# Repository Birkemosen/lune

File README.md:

# Lune V6

Local 6-zone hydronic manifold controller (ESP32-S3 / ESPHome). Safe without a
coordinator: motors, endstops, temperature freshness, and command clamps run on
the device.

**Documentation:** [docs/README.md](docs/README.md) — index of all V6 documentation, with links to Lune Touch and the design system.

> **Status (October 2026): pre-release, in field validation.**
>
> | Area | State |
> |---|---|
> | Firmware | `v1.0.0` development builds; no public release yet |
> | Hardware | Rev 3.3 is the only supported board |
> | Valve control | Endstop detection, working-range learning and motor fault handling in place |
> | Web UI | Local web UI (EN/DA): Home, a sheet per zone and the manifold, and System (connections, firmware, backup, service, Motor Lab) |
> | Integration | `/api/v1` with Touch authority lease, Asgard heat-pump coordination and external room temperatures |
> | Implementation plan | Phases 0–8 complete; phase 9 (staged field rollout and outcome measurement) in progress |
>
> Expect breaking changes to the API and persisted settings until `v1.0.0` is tagged.

## Layout

```text
lune-v6/                 Firmware, local dashboard, hardware, tests
  configurations/        Device YAML entrypoints
  packages/              Board / hardware / network / zones
  components/            Custom C++ (lv6_*)
  web/                   Design System 2 UI (see below)
  docs/                  Manual, API, architecture
shared/contracts/        Cross-product contracts (e.g. room physics)
docs/                    Cross-device notes
```

Related repositories:

- [`Birkemosen/lune-coordinator`](https://github.com/Birkemosen/lune-coordinator) —
  Lune Touch / Mini, the whole-house coordinator.
- [`Birkemosen/lune-design-system`](https://github.com/Birkemosen/lune-design-system) —
  shared UI tokens and CSS. The web UI build expects it as a sibling checkout at
  `../lune-design-system`.

## Web UI (Lune Design System)

Home / sheets / System on the Lune design system: static HTML/CSS with radio navigation;
a thin binder paints live `/api/v1` data.
No ESPHome entity REST from the UI.

```text
lune-v6/web/
  build_ui.py       i18n shell → ui/{en,da}/
  i18n/             en / da catalogues
  binder-src/       esbuild → ui/binder.js (+ dashboard.js alias)
  ui/               Built CSS, HTML, binder (embedded in firmware)
  preview.html      Local mock preview
```

```bash
make design-tokens     # → lune-v6/web/ui/lune-ui.css
make dashboard-build   # HTML + binder + preview.html
```

Preview without a device:

```bash
python3 -m http.server 8765 -d lune-v6/web
# → http://127.0.0.1:8765/preview.html
```

Installer help: [`lune-v6/docs/Manual.md`](lune-v6/docs/Manual.md) (linked from in-UI `?`).

## Hardware (rev 3.3)

Current board package: `lune-v6/packages/board/lune-v6-rev33.yaml` (`rev33_gpio`).
Two-layer USB-C ESP32-S3-WROOM-1-N8R8 controller, six 3.3 V valve channels
(3× DRV8411 + hardware one-hot decoder), shared high-side sense for ADC /
ripple / overcurrent. Hostname: `lune-v6-<mac>` (revision is not part of the
name).

See [`lune-v6/README.md`](lune-v6/README.md) and
[`lune-v6/hardware/lune-v6-rev3.3/`](lune-v6/hardware/lune-v6-rev3.3/) for the
revision table, ECO level, and firmware integration. The firmware is for Rev 3.3
only and refuses to drive motors on an older board — pin maps collide.

Validate the schematic:

```bash
python3 lune-v6/hardware/lune-v6-rev3.3/check_design.py
```

## Setup and commands

```bash
python3.13 -m venv .venv313
./.venv313/bin/python -m pip install -r requirements.txt
```

From the repository root (defaults to Lune V6):

```bash
make config
make dashboard-build
make build
make test
make deploy HOST=192.168.x.x
```

Device-local:

```bash
make -C lune-v6 help
make -C lune-v6 test
```

Release firmware (no WiFi secrets) → gitignored `lune-v6/dist/`:

```bash
make release-firmware VERSION=v1.0.0
```

`secrets.yaml` stays at the repo root and is gitignored.

## Boundaries

- V6 validates and clamps every command locally.
- Touch sends setpoints / weather preload — not zone choice for room temperatures.
- External hubs POST `/api/v1/room-temperatures` with `sensor_id`; V6 maps to zones.
- Shared physics contract: [`shared/contracts/lune_room_physics_contract_v1.md`](shared/contracts/lune_room_physics_contract_v1.md).

## License

| Part | License |
|---|---|
| Firmware, web UI, scripts and documentation — everything not listed below | [GPL-3.0-or-later](LICENSE) |
| Hardware design in [`lune-v6/hardware/`](lune-v6/hardware/) — EasyEDA project, schematics, design contract, layout and review documents | [CC BY-NC-SA 4.0](lune-v6/hardware/LICENSE) |

Third-party files keep their own licenses — notably the ESPHome agent skill in
[`.agents/skills/esphome/`](.agents/skills/esphome/) (MIT).

You may build, modify and share the firmware under the GPL; derived firmware must stay
open under the same terms. The firmware is built on ESPHome, whose runtime is GPLv3.

The hardware design is **non-commercial**. As the licensor I read that as follows:

- **Allowed:** private individuals may have boards made — by a PCB fab or assembly
  service ordering on their behalf — and use them in their own home. Fabs sell in
  minimum batches, so passing surplus boards from your own order to other private
  individuals is fine **at cost or for free**, as long as nobody makes money on it.
- **Not allowed without a commercial license:** selling boards, kits or installed systems
  for profit, offering them as part of a paid service or installation, or any other use
  aimed at earning money from the design.

Modified designs must be shared under the same license. If you want to use the design
commercially, ask through [GitHub](https://github.com/Birkemosen).

## Name

"Lune" and "Lune V6" identify this project. Forks are welcome under the licenses above,
but please give them a different name and do not present them, or products built on
them, as Lune or as endorsed by this project.

## Support the project

Lune is developed in spare time and paid for out of pocket. If it heats your floors and
you want to give something back, you can sponsor it through
[GitHub Sponsors](https://github.com/sponsors/Birkemosen).

If you build a Lune V6, a small one-time thank-you is welcome but never expected.
Sponsoring comes with no rewards or promises: Lune is built at its own pace.

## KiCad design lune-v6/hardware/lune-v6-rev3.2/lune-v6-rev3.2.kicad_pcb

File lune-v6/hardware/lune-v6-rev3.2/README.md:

# Lune V6 Rev 3.2

Status: ECO level **rev3.2-H**; PCB placed and routed; DRC, fabrication export
and physical qualification pending.

**Source of truth: `EasyEdaPro/lune-v6-rev3.2.eprj`, PCB document `pcb1_1`.**
Rev 3.2 was authored in KiCad through ECO rev3.2-B and every ECO from rev3.2-C
onward was done in EasyEDA Pro. The KiCad sheets, generator, exported netlist and
ERC report were deleted once keeping both live produced a schematic/PCB
divergence no gate could see; they remain in git history, and
`design-contract.json` → `designator_history` maps every old reference to the
designator the board carries.

Rev 3.2 is the successor to Rev 3.1 Lean. It retains the compact, two-layer,
six-channel manifold controller with an embedded `ESP32-S3-WROOM-1-N8R8`. The
design deliberately optimizes populated component count without removing
independent endpoint evidence or hard safety layers.

ECO **rev3.2-B** supersedes the first Rev 3.2 schematic. It corrects the
commutation tacho, re-references the independent runtime cutoff, and removes
three parts that were not earning their place. See
[design-review.md](design-review.md) for the findings behind each change and
§ [ECO rev3.2-B](#eco-rev32-b) below for the change list. Seven further ECOs have
landed since; each has its own section below, and the schematic is at
**rev3.2-H**.

## Decision

- Six channels, because that is the actual product need. Channels seven and
  eight do not reduce feeder count enough to justify their connectors, driver,
  protection and board-edge area.
- Three dual H-bridges, `DRV8411PWPR`, with no DNP second-source pads: the
  DRV8411 integrates its charge-pump and regulator capacitors, so pins 11 and 14
  stay open. `DRV8410PWPR` is the nominated second source - pin-compatible
  including those NC pins - but is not stocked at LCSC. DRV8833 was dropped in
  ECO rev3.2-E; see `driver.alternatives_evaluated` in the contract.
- One active-high 4-to-16 decoder gives a physically one-hot drive path:
  `Q0..Q5` drive one direction and `Q8..Q13` the opposite direction.
- One calibrated, shared high-side current channel measures force. Its raw,
  AC-coupled commutation ripple feeds a dedicated band-pass amplifier and
  comparator and an ESP32 counter input, so every selected-motor commutation
  can be counted. The tacho function is 14 mounted parts: one single op-amp,
  nine resistors and four capacitors. It reuses the spare `LMV393` comparator
  channel and the existing shunt; there are no per-motor sensors or extra mux.
- The amplified ripple is also brought to `GPIO1` as `ADC_TACHO` through one
  resistor. That
  makes the qualification programme practical - the § 2 and § 3 edge-rate
  measurements can be logged by the device itself instead of needing a scope on
  every board, actuator and temperature combination - and it gives firmware an
  independent digital cross-check on the hardware comparator.
- The Rev3.1 BEMF mux, terminal resistor arrays, buffer and ADC clamp are
  deliberately omitted: they added ten mounted parts, one ADC GPIO and a coast
  interruption, while position learning is now continuous from `COMM_TACHO_N`.
- Endpoint classification requires direction-specific current, continuous
  commutation count/plateau, and a learned-count endpoint window. Current
  alone is never accepted as an endpoint.
- Fixed per-bridge current regulation, a fixed rail overcurrent comparator,
  persistent hardware fault latch and firmware runtime limits form nested
  protection layers. There is deliberately **no** hardware max-on-time; ECO
  rev3.2-C removed it on a hazard assessment recorded as
  `actuator_overrun_hazard`.
- Base board has LED status and an unpopulated `GND/3V3/SCL/SDA` display header
  (`J8`). A fixed OLED is not populated: it costs board area and assembly money
  without improving local heating safety. The bus pull-ups **are** on the board
  (ECO rev3.2-F) so SDA and SCL cannot float when no display is fitted.
- A protected three-pin `3V3/1-WIRE/GND` service connector supports external
  supply and return temperature probes. Both the data line and the supply pin
  have a series resistor and a local 3.3 V TVS; temperature freshness remains a
  firmware safety requirement, not a substitute for motor endpoint evidence.

## ECO rev3.2-B

Every item is verified by `check_design.py`, which fails if any of them is
reverted.

| # | Change | Why |
|---|---|---|
| 1 | Tacho comparator hysteresis moved from the threshold input to the non-inverting input (`R15` now bridges `COMM_TACHO_N` to `TACHO_CMP`) | Feedback to the inverting input is negative feedback. As drawn it was a relaxation oscillator with a 144 mV chatter band, not a Schmitt trigger - and PCNT counts that chatter. |
| 2 | Tacho stage rebuilt as a band-pass: high-pass 1.6 Hz (was 15.9 Hz), in-band gain ~85 (was 11), new 339 Hz low-pass | Measured commutation is 20-40 Hz at 14-19 mA, i.e. 7-30 mV at `CURRENT_RAW`. The old corner sat inside the signal band, the old gain matched the hysteresis, and nothing rejected the 50 kHz current-regulation chop. Now -43 dB at the chop. |
| 3 | `TACHO_REF` is a stiff 1k/1k mid-rail bypassed by 22 µF (was 47k/47k + 1 µF) | The gain-setting return used to see a 23.5 kΩ source impedance, so gain fell to ~6.6 at 20 Hz, and comparator transitions injected back into the reference. |
| 4 | ~~74HC4060 master reset moved to `LATCH_STATE`~~ | **Superseded by ECO rev3.2-C** — the whole timer block is removed. |
| 5 | ~~Timing set `Rt = 180k`, `Rs = 360k`, `Ct = 22 nF C0G` on `Q14`~~ | **Superseded by ECO rev3.2-C** — the C0G reasoning was right, but the oscillator was wired rotated one position around the star, so 71.4 s was never what the board would have made. |
| 6 | Rail overcurrent comparator senses `CURRENT_RAW` instead of the filtered ADC node | An output-to-GND short bypasses the xISEN resistor and the DRV8411 OCP is 4 A, so this comparator is the only fast protection for that fault. The 1k/100n filter was adding 100 µs to it. |
| 7 | `D1` BAT54S ADC clamp removed | The INA180 runs from `+3V3_ANALOG` and cannot drive the node outside 0-3V3, so the clamp protected nothing, while its reverse leakage through `R1` added a temperature-dependent offset that room-temperature calibration cannot remove. |
| 8 | `R3`/`R4` 22 Ω USB series resistors removed | ESP32-S3 native USB drives D+/D- directly in Espressif reference designs; 22 Ω moved the single-ended impedance away from the ~45 Ω target for no protection benefit. |
| 9 | `C41` 220 µF electrolytic replaced by a second stocked 22 µF ceramic | The actuator draws 14-19 mA running and 23-50 mA stalled. This removes the only wet part, the tallest passive (7.7 mm) and one BOM line. |
| 10 | `J1` supply pin fed through `R22` 33 Ω + `D2` TVS as `+3V3_EXT` | It used to be a bare tap on the ESP32's own rail, so a shorted or ESD-struck field wire hit the MCU supply directly - against S-06. |
| 11 | Native `(dnp yes)` / `(in_bom no)` attributes now emitted | DNP intent lived only in a text property, so a generated BOM/CPL would have ordered and placed the six second-source capacitors and tried to place twelve test pads. |
| 12 | `check_design.py` added; `C46` DNP pad and ~130 lines of dead generator code removed | Rev 3.2 shipped without the Rev 3.1 audit scripts, which is why the placement counts in this file drifted by ten parts. |

Feeder consolidation: the tacho rebuild uses only values already in the BOM, so
the unsourced 47k and 2.2M values are gone. Net BOM lines are down by two
(22 Ω, BAT54S and the electrolytic out; 22 nF C0G in). The C0G timing capacitor
left again with the whole timer block in ECO rev3.2-C, so no open sourcing items
remain; `check_design.py` fails if that declaration goes stale.

## ECO rev3.2-C - the runtime cutoff is removed

The 74HC4060 timer block - six parts, **~100 mm2**
of courtyard out of the congested west block - is deleted, plus the `TIMEOUT_Q14`,
`TIMER_RTC`, `TIMER_RS`, `TIMER_CTC` and `TIMING_COMMON` nets and one
characterization gate.

> Its KiCad designators were `U36`, `R27`, `R28`, `C25`, `Q2` and `C24`. Do not
> use those as a regression guard: the EasyEDA scheme reuses `R27`, `R28` and
> `C25` for unrelated parts. `check_design.py` guards the removal by device
> (`actuator_overrun_hazard.removed_devices`), which is what it should always
> have been.

This is a hazard-assessment result, recorded as `actuator_overrun_hazard` in the design
contract. Two things drove it:

- **The hazard is bounded and not electrical.** An over-driven actuator strips its own
  gear train, in the *opening* direction only. A parted head leaves the valve insert and
  its seal in the manifold, releasing the pin to full flow - closed system, no escape, and
  the loop cannot exceed the mixing-valve supply temperature. Worst case is one actuator,
  and it announces itself. The rail comparator never helped here: stall current sits below
  its 280 mA trip, and the damage mechanism is torque x duration while the comparator
  bounds current.
- **The part cost more than it saved.** Its oscillator was wired rotated one position
  around the timing star, invisible to ERC and to `check_design.py` because the timeout
  was computed from contract values rather than schematic topology. And bounding *total
  armed time* collided with learning mode, which needs 43-85 s to reach both end stops
  against a 56-86 s cutoff - so commissioning could latch a fault firmware cannot clear.

Retained: the firmware runtime limit already in service, the commutation tacho as
rotation/stall evidence, the ESP32 task watchdog, and `R26`-`R31` for a defined safe state
when GPIOs go high-Z. The **fault latch stays** - `U2` pin 6 is the only consumer of
`FAULT_N_RAW`, which five sources feed, so `check_design.py` now asserts that consumer and
those contributors as an invariant.

One behavioural change: the latch no longer self-disarms when idle. That is benign -
`MOTOR_ENABLE` falling to its 100 k pulldown drives `DECODER_INHIBIT` high and the 4514
turns every output off regardless of `DRIVE_PERMIT`.

## ECO rev3.2-D - decoder package, placement and address map

`U28` goes from `XL74HC4514D` in **SOIC-24W** to Nexperia **`74HC4514PW,118`** (`C58910`,
TSSOP-24). Same logic, same pin numbering, so the netlist is unaffected by the package
change itself.

| | Courtyard |
|---|---|
| `SOIC-24W` | 188.6 mm² |
| `TSSOP-24` | **63.9 mm²** (66% less) |

Two smaller chips were considered and rejected. Active-low decoders (`'138`, `'139`, `'137`,
`'4515`) are out on safety grounds: with active-low outputs, idle becomes `IN1=IN2=1`, i.e.
**brake on all six channels**, and `DECODER_INHIBIT` would assert brake rather than release
to coast. Shift registers (`'595`) give a three-wire bus and lovely routing but let firmware
write any pattern, which destroys the structural one-hot guarantee - and one-hot is load
bearing for the *measurement* too, since the shared shunt would otherwise sum two motors and
the commutation tacho would count garbage. That leaves only `74HC4514` and `74HC237`, and two
`'237` cost more copper (232 mm vs 200 mm) and more area (84.7 mm² vs 63.9) because you trade
four long output runs for five long bus runs.

### Placement and remap

`U28` moves from east of the module into the gap between `U9`'s and `U10`'s VM-cap
clusters**, unrotated, at the driver row's latitude. Its pin rows then run north-south and
each flank faces the drivers it serves - side A west to `U9`, side B east to `U10` then
`U11` - so **no output crosses the package**. Output trace budget falls from ~540 mm spanning
the whole board to ~120 mm beside the drivers.

The address-to-output assignment is remapped to suit that geometry. `MOTOR_TERM_DIR` is
renamed **`MOTOR_ADDR3`**: keeping bit 3 as the direction bit is exactly what forced every
motor's forward/reverse pair to straddle the package, because Q0-Q7 all sit on side A and
Q8-Q15 on side B. And addresses **0-3 are unreachable by design** - side A keeps four spare
outputs rather than being packed, since packing them would move a driver's signals onto the
flank facing away from it. `check_design.py` asserts that `Q0`-`Q3` reach no bridge input.

> ~~`address = (channel_code << 1) | direction`, direction 0 = forward, so bit 0 is the
> direction bit and firmware needs only a six-entry code table.~~ **Superseded by the
> as-built assignment.** Routing `U28` north-around - outputs leave the flank, pass north of
> the package, run along and drop south into the driver input row - puts the southernmost
> decoder pin in the southernmost lane serving the *nearest* destination, which inverts the
> order against a straight-across layout. Direction then tracks bit 0 only on odd channels
> and inverts on even ones, because the mirrored bridge order swaps the FWD/REV sense
> between motor A and motor B of each driver. **No bit encodes direction.**

The as-built map is `decoder.channel_address_map` in `design-contract.json`, which
`check_design.py` asserts against the schematic, and firmware uses those twelve entries
rather than a formula (`REV32_FORWARD_ADDRESS` / `REV32_REVERSE_ADDRESS` in `rev32_logic.h`,
asserted against this table by `make test-rev32-logic`):

| Channel | Forward | Reverse |
|---|---|---|
| 1 | 7 | 6 |
| 2 | 4 | 5 |
| 3 | 13 | 12 |
| 4 | 14 | 15 |
| 5 | 9 | 8 |
| 6 | 10 | 11 |

## ECO rev3.2-E - the six DNP second-source pads are removed

`C110`-`C112` (VINT, 2.2 µF) and `C114`-`C116` (VCP, 10 nF) are deleted, and `DRV8411`
pins 11 and 14 are left open. `check_design.py` now asserts that **no DNP placement
remains**, so they cannot come back quietly.

They existed to keep the pin-compatible `DRV8833` available as a shortage substitute. TI
now lists `DRV8411` as the **newer replacement for** `DRV8833` — pin-for-pin with the same
functionality, adding integrated VCP and VINT capacitors, 1.8 V logic inputs and ultra-low
sleep current. So the pads preserved the *older* part, which carries more EOL risk than the
one it was backing up.

And this contract had already argued the substitute was not viable: 2.0× the unit price,
0.35× the stock, six extra capacitors, and — decisively — no specified `xISEN` trip limits
with `RDS(on)` explicitly derated below `VM = 5 V`. On a 3.18 V motor rail the DRV8833 is
unspecified in exactly the current-ceiling role it would have had to fill.

The nominated second source becomes **`DRV8410`**, which is pin-compatible *including* the NC
pins 11 and 14 — so it needs no external capacitors and drops in with no board change. It is
not stocked at LCSC today; that is the open item, not the pads.

### What it buys

| | Before | After |
|---|---|---|
| Placements | 114 + 6 DNP | **114, no DNP** |
| Nets | `VINT1-3`, `VCP1-3` | gone |
| Decoder gap | 9.90 mm | **16.90 mm** |
| Clearance each side of `U28` | 1.10 mm | **4.60 mm** |

The two pads per driver at `dx ± 6.5` were what pinned the decoder gap. Removing them also
clears the **y = 35.5 band**, so the `FWD`/`REV` fan-out heading east now crosses only
`+3V3_MOTOR` instead of three traces per driver — the crossing problem the previous ECO was
working around disappears rather than being solved.

## ECO rev3.2-F - connector-driven pin moves, I2C pull-ups, JST pads

Four signals move so that each sits on the side of the module its connector is on, and
so that nothing digital occupies an ADC1 channel:

| Net | Pad | GPIO | Why |
|---|---|---|---|
| `MOTOR_ENABLE` | 18 → **8** | 10 → **15** | Off ADC1, and onto the west row beside the latch block it feeds. *Moved again in rev3.2-H to pad 11 / GPIO18.* |
| `ONEWIRE_MCU` | 35 → **11** | 42 → **18** | Connector moved beside USB-C on the west edge; frees a JTAG pin. *Moved again in rev3.2-H to pad 12 / GPIO8.* |
| `I2C_SDA` | 12 → **23** | 8 → **21** | Display connector goes east; frees an ADC1 channel |
| `I2C_SCL` | 17 → **24** | 9 → **47** | Same, and adjacent to SDA on the module's south edge |

**ADC1 is now reserved for analog.** It is `GPIO1`–`GPIO10` and the only ADC usable while
WiFi runs; ADC2 (`GPIO11`–`GPIO20`) is not, which is where slow digital belongs. Only
`ADC_TACHO` (1), `ADC_CURRENT` (2) and one declared exception sit on ADC1, leaving **six
spare channels**. `check_design.py` asserts the rule, so a future pin move cannot quietly
eat an analog channel — which is exactly what these three signals were doing.

Exceptions are declared data, not a code exemption: they live in `design-contract.json`
under `adc1_digital_exceptions`, and `check_design.py` prints each one on every run and
fails if a listed signal is no longer on ADC1, so the list cannot go stale. There is one —
`STATUS_LED_N` on `GPIO4` (§ [ECO rev3.2-G](#eco-rev32-g---status_led_n-moves-off-the-south-row))
and `ONEWIRE_MCU` on `GPIO8` (§ [ECO rev3.2-H](#eco-rev32-h---two-pin-moves-and-the-console-series-resistors)).
Two analog channels, two exceptions, five spare.

### I2C pull-ups added

`R37`/`R38`, 4k7 to `+3V3_LOGIC`. The bus had none. They are not optional and not only for
the bus to function: without them `SDA` and `SCL` float on the ESP32's inputs whenever no
display is fitted, which is the failure `R26`–`R29` exist to prevent at the decoder — a
floating CMOS input sits near mid-rail with both transistors conducting. A display module
carrying its own pull-ups gives 2k35 effective, still inside spec, and a 100 ns rise into
50 pF against the 300 ns that 400 kHz allows.

### Two unpopulated JST footprints replace eight test pads

`TP30`–`TP37` are gone. In their place:

| | Pins | Footprint |
|---|---|---|
| `J8` display I2C | GND, +3V3_LOGIC, SDA, SCL | `JST_PH_S4B-PH-SM4-TB_1x04-1MP_P2.00mm_Horizontal` |
| `J9` UART console | GND, +3V3_LOGIC, TXD0, RXD0 | same |

Both are `COPPER_ONLY`: the pads exist, nothing is ordered or placed, and a connector gets
soldered on only when a display or a console is actually wanted. Side-entry SMD so no drill
holes cut the ground pour, and PH's 2.00 mm pitch is the most hand-solderable JST — which is
the whole point of pads you fit by hand. Copper-only items go from 14 to 8.

## ECO rev3.2-G - STATUS_LED_N moves off the south row

`STATUS_LED_N` moves from module **pad 25 (`GPIO48`)** to **pad 4 (`GPIO4`)**. Nothing about
the LED changes: `D3` is still a plain green `KT-0805G` sinking through `R23` 1 k from
`+3V3_LOGIC`, still active low. Only the pin and therefore the escape direction change.

**It is a layout change, not an electrical one.** On pad 25 the net left the module on the
south row, which put `D3` and `R23` in the `x 49–52 / y 38–43` pocket, and `R23`'s supply
tap is what drags the `3V3_LOGIC` spine up to `y = 37.21`. That pocket is the only room
available to re-arrange the `3V3_LOGIC`, `VBUS_PROTECTED` and `3V3_MOTOR` spines, which
today leave a single one-trace-wide lane between them. `UART_TX_DBG`, `UART_RX_DBG`,
`I2C_SDA` and `I2C_SCL` are all still unrouted and none of them has a top-layer route
while that lane is one wide. Pad 4 leaves west instead, clear of the band entirely.

**It spends an ADC1 channel, and that is the cost.** `GPIO4` is `ADC1_CH3`, so the move
needs the declared exception described under the ADC1 reserve above. No cheaper pin exists:

| Pads | GPIOs | Why not |
|---|---|---|
| 5, 6, 7, 12 | `IO5`–`IO7`, `IO8` | Same ADC1 reserve — no better than pad 4 |
| 15, 17, 18 | `IO3`, `IO9`, `IO10` | ADC1 as well, and `IO3` is a strapping pin |
| 16, 26 | `IO46`, `IO45` | Strapping. The LED pulls its pin high through 1 k at reset, which on `IO46` suppresses the ROM log and on `IO45` selects 1.8 V `VDD_SPI` |
| 28, 29, 30 | `IO35`–`IO37` | Octal PSRAM |
| 32–35 | `IO39`–`IO42` | Free, but on the east side with the analog island — the wrong direction |

The BEMF frontend that would have wanted a third analog channel was removed in Rev 3.2, so
the reserve had the headroom. Two analog channels and one exception leave six spare.

**Firmware.** `lune.yaml` still declares `pin_rgb_status_led: GPIO48` and also
`pin_nfault: "4"`. The rev3.2 migration already marks `pin_nfault` for deletion; both edits
must land together or `GPIO4` is assigned twice. See § Migration status in
`../../README.md`.

## ECO rev3.2-H - two pin moves and the console series resistors

Three changes, all of them layout consequences that the schematic has to record.

### `MOTOR_ENABLE` pad 8 → 11, `ONEWIRE_MCU` pad 11 → 12

The safety cluster that `MOTOR_ENABLE` feeds sits at one latitude: `U7` at
`y = 49.01`, `R30` at `48.90`, `Q1` at `49.04`. Module pad 11 is at `y = 49.19`,
so from there the net is a straight west line. From pad 8 at `y = 53.00` it had
to drop 4 mm across the escapes of pads 9 and 10 - `LATCH_STATE` and
`LATCH_ARM`, the two nets it least wants to cross. `ONEWIRE_MCU` followed onto
pad 12.

**It costs an ADC1 channel.** Pad 12 is `IO8`, which is the channel `I2C_SDA`
was moved off in rev3.2-F, so this partly reverses that move. The difference is
what sits there now: `I2C` is a live bus on every boot, while 1-wire is a
15 kbit/s field bus behind a 33 Ω series resistor and a TVS. Of the two, it is
the cheaper one to put back.

No cheaper pin exists. Every other free pad on the west and south rows is either
an ADC1 channel (15/17/18 = `IO3`/`IO9`/`IO10`) or a strapping pin (16/26 =
`IO46`/`IO45`); pads 28-30 are the octal PSRAM; pads 32-35 sit east with the
analog island. The move is declared in `adc1_digital_exceptions`, so
`check_design.py` prints it on every run and fails if it ever stops being true.

### `R39`/`R40`, 1 kΩ in series with the console

`J9` sits 34 mm east of the module and the run crosses the analog island's
south flank. `TXD0` is a full-speed CMOS output with roughly 2 ns edges; 1 kΩ
against the ~40 pF the run presents stretches that to about 90 ns, which is 1 %
of a bit at 115200 and removes the harmonic content the ADC and tacho nodes
would otherwise see. Both resistors sit at the module end so the whole run is
damped. The `RXD0` one is pin protection rather than edge rate - that edge is
driven by whatever adapter is plugged in.

1 kΩ is already a BOM line six times over (`R1`, `R8`, `R11`, `R12`, `R13`,
`R23`), so this adds no part number.

**Consequence for net names:** `UART_TX_DBG` and `UART_RX_DBG` now name the
**header** side. The module side is `UART_TX` and `UART_RX`, and that is
what the `gpio` map tracks. Pads 36/37 are `RXD0`/`TXD0` - the ROM bootloader
console - and cannot move.

### Antenna cutout 21 → 22 mm

The notch was cut 1 mm wider than specified, so the module gets 2.0 mm of air
either side instead of 1.5. That is margin, not a defect; the contract now
records what the board has. Ground copper and stitching run up to the cut on
both flanks and along its south edge at a 2 mm pitch.

### Also corrected in this ECO

`pcb.block_placement` still described the Rev3.1 arrangement, with the analog
block in the west. The rev3.2 pin reassignment moved `ADC_CURRENT` and
`ADC_TACHO` to the module's east row and the block followed; the contract now
carries the as-built positions. `firmware-integration.md`'s pin table had
drifted on five entries and is now generated from the same `gpio` map that
`check_design.py` asserts.

## Size and assembly target

- 2 layers, `90 x 75 mm`, within the JLCPCB `100 x 100 mm` price class.
- Four M3 holes form a symmetric `82 x 67 mm` rectangle. The six RJ9 body
  outlines are centered as a row along the bottom edge and project 1.0 mm;
  USB-C is rotated 90 degrees counter-clockwise and projects 1.0 mm at the
  left edge; the 1-wire terminal projects 1.75 mm at the right edge.
- The tacho components must be placed adjacent to the existing current-sense
  amplifier and kept away from motor loops and the current ADC. Copper, pours,
  thermal design and final placement remain a Rev3.2 layout task.
- **116 populated placements**, no DNP parts, 8
  copper-only pads and 4 mounting holes. The DRV8833 substitute population is
  117. No electrolytic parts; tallest passive is 1.45 mm.
- The final footprint total, assembly price and manufacturing files are
  deliberately not projected until the Rev3.2 PCB exists.

## Release state

Rev 3.2 is a schematic-only ECO. The Rev 3.1 routed PCB, Gerbers, BOM and CPL
do not include the Rev 3.2 analog changes and must not be fabricated as
Rev 3.2.

Firmware exists and is the default Lune V6 build: `configurations/lune-v6.yaml`
(hostname `lune-v6-<mac>`). The board package `packages/board/lune-v6-rev32.yaml`
selects the `rev32_gpio` backend, which owns the 4-bit decoder, the per-move latch arm,
the 6 dB `ADC_CURRENT` range and PCNT capture on `COMM_TACHO_N`. Automatic startup
calibration stays off - the thresholds are bring-up values, and the tacho's
missed/false-edge rate is unmeasured. Neither revision's entrypoint may be
flashed on the other's hardware; see the collision table in
`firmware-integration.md`. Remaining release gates are:

1. ~~Close the open items `check_design.py` reports.~~ **Done** - the gate passes.
2. Run DRC to zero errors and zero unrouted nets, then export Gerber, BOM and
   CPL into this folder so the fabrication package is reviewable in git. These
   are the three gates `check_design.py` deliberately does not claim to cover.
3. Capture the raw shunt commutation spectrum on supported actuators and
   confirm the band-pass, hysteresis and counter pulse-rejection limits against
   measurement.
4. Characterize both endpoint directions on every supported actuator sample,
   including cold/hot, supply tolerance, already-at-stop, jam, disconnect and
   cable-transient cases.
5. Qualify the external 1-wire cable and supply/return probes for ESD, open,
   short, stale data and sensor substitution faults.
6. Settle the deferred production decisions: the `xISEN` value once § 3 has the
   current distributions, the TPS2553 fault-response variant, and a resettable
   PTC on the 1-wire supply branch. The motor-output ferrite rating is settled -
   200 mA is kept, see `motor_output_ferrites.derating_decision`.
7. Add a copper-only pad on `FAULT_N_RAW`. It reaches no GPIO and, on the
   as-built board, no test pad either, so neither firmware nor a scope can see
   which source faulted.

## Verification

EasyEDA Pro is the source of truth. `check_design.py` reads the project file
directly - placements, net connectivity, BOM flags, symbol pinouts and the
routed geometry - and asserts it against `design-contract.json`:

```sh
python3 check_design.py
```

It checks the **PCB** document rather than the schematic on purpose. The PCB is
what becomes Gerbers, and every defect class this gate exists to catch is a
property of what gets fabricated. Checking the schematic instead would let a
schematic/PCB divergence pass, which is what happened while KiCad and EasyEDA
were both live: 57 of 79 nets matched, and the differences included twelve
undocumented series ferrites and a changed motor-connector pinout.

`netlist-golden.json` is a committed snapshot of every pad-to-net connection.
Any edit that alters connectivity fails loudly instead of passing as a layout
that merely looks plausible. Regenerate it only when a change is intended:

```sh
python3 check_design.py --update-golden
```

Three gates stay with the editor because the project file does not record them:
**DRC to zero errors**, **zero unrouted nets**, and the **Gerber/BOM/CPL
export**. `validation-plan.md` § 1 owns them; `check_design.py` prints a
reminder rather than pretending to cover them.

Designators were renumbered when the source of truth moved. Documentation
written before ECO rev3.2-G may still use the KiCad names;
`design-contract.json` → `designator_history` maps all 118 of them.

See [rev2-review-addendum.md](rev2-review-addendum.md),
[architecture.md](architecture.md), [design-review.md](design-review.md),
[validation-plan.md](validation-plan.md),
[firmware-integration.md](firmware-integration.md),
[design-contract.json](design-contract.json), and the five generated schematic
sheets. `layout-audit.md` is retained as Rev3.1 historical evidence only; it
does not validate the Rev3.2 analog ECO.

## Drawing convention, and why two findings stayed invisible

Rev 3.2-A was authored in KiCad and carried 100% of its connectivity on global
labels attached to pins: zero wires, zero junctions, zero hierarchical sheet
pins. That is electrically valid but it is a netlist rendered as text, and it is
why two findings survived review. B1 - the tacho hysteresis resistor landing on
the comparator's threshold input instead of its signal input - is something a
drawn feedback loop shows at a glance and a label cannot show at all. B6 - the
amplifier drawn with the wrong TLV9001 pinout variant - is the same class: it
made a wrong drawing look right, and pointed ERC at the wrong pins.

Two rules came out of that and both outlived the tool:

- **Local sub-circuit topology gets drawn**, not labelled. Dividers, RC
  networks, the amplifier feedback loop, the comparator hysteresis, the arm
  path, the sense resistors, the USB data pairs, the inhibit node. Rails and
  cross-sheet fan-out keep names.
- **Every net carries a name.** A wired-but-unnamed net is invisible to
  documentation and to the golden-netlist guard, and it cannot be discussed in
  a review. `check_design.py` asserts this; seven nets arrived from the KiCad
  import without labels and are still open.

The mechanical guard against the B6 class is now `pcb.symbol_pinouts` in the
contract, asserted against the project's own symbol library. It covers the two
5-pin amplifiers, the comparator and the status LED - the LED because pin 1 is
the anode in this library and the cathode in KiCad's, so the two schematics
disagreed on paper while both boards were in fact correct.

## Schematic sheets

Five sheets in `EasyEdaPro/lune-v6-rev3.2.eprj`, asserted by
`pcb.schematic_sheets`:

- `power` — USB input protection and the power rails.
- `controller` — ESP32, one-hot decoder and safety logic.
- `motors` — the three dual H-bridges, six outputs, ferrites and TVS clamps.
- `analog` — current sensing, safety latch and commutation tacho.
- `connectors` — actuators, sensors, service header and test pads.

The board is the `pcb1_1` document. A second document, `pcb1`, is a near
identical earlier copy and must be deleted: two PCB documents in one project is
a Gerber-export hazard, and `check_design.py` fails while both exist.

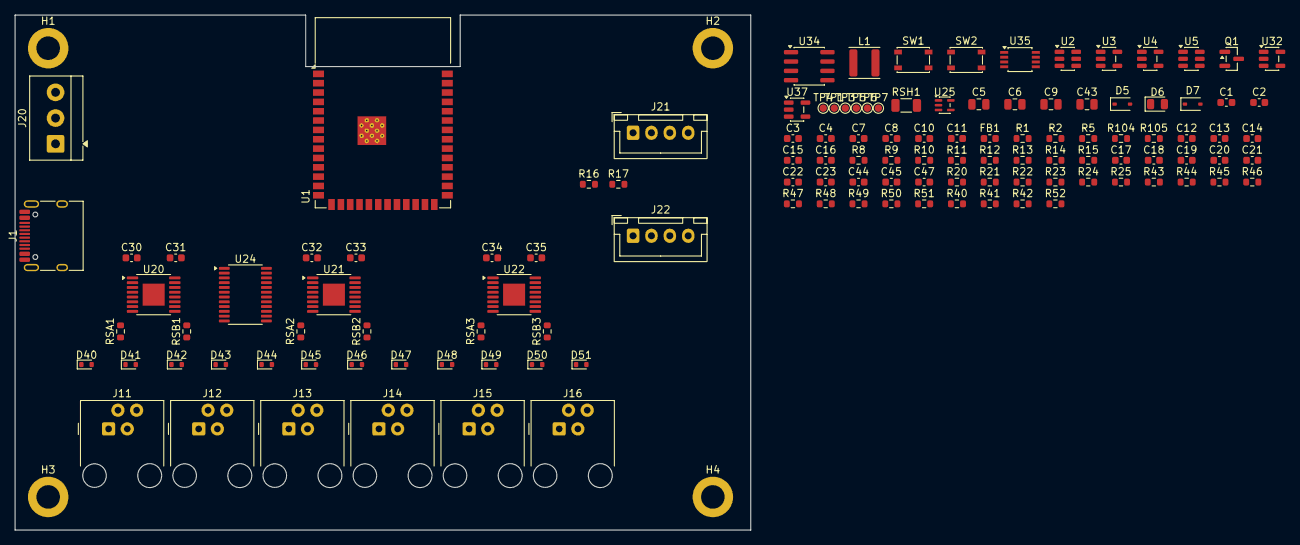
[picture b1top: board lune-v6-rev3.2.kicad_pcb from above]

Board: 2 copper layers, 100.0 x 70.0 mm, 128 parts (0 on the bottom side), 77 nets, no tracks yet.

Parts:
C1, C2, C3, C4, C7, C8, C10, C11, C12, C13, C14, C15, C16, C17, C18, C19, C20, C21, C22, C23, C30, C31, C32, C33, C34, C35, C44, C45, C47: C_0603_1608Metric
C5, C6, C9, C43: C_0805_2012Metric
D5, D7: D_SOD-323
D6: LED_0805_2012Metric
D40, D41, D42, D43, D44, D45, D46, D47, D48, D49, D50, D51: D_SOD-523
FB1: L_0603_1608Metric
H1, H2, H3, H4: MountingHole_3.2mm_M3_ISO14580_Pad
J1: USB_C_Receptacle_HRO_TYPE-C-31-M-12
J11, J12, J13, J14, J15, J16: RJ9_Evercom_5301-440xxx_Horizontal
J20: TerminalBlock_4Ucon_1x03_P3.50mm_Horizontal
J21, J22: JST_XH_B4B-XH-A_1x04_P2.50mm_Vertical
L1: L_Sunlord_SWPA4018S
Q1: SOT-23
R1, R2, R5, R8, R9, R10, R11, R12, R13, R14, R15, R16, R17, R20, R21, R22, R23, R24, R25, R40, R41, R42, R43, R44, R45, R46, R47, R48, R49, R50, R51, R52, R104, R105: R_0603_1608Metric
RSA1, RSA2, RSA3: R_0603_1608Metric
RSB1, RSB2, RSB3: R_0603_1608Metric
RSH1: R_1206_3216Metric
SW1, SW2: SW_SPST_PTS810
TP1, TP3, TP4, TP5, TP6, TP7: TestPoint_Pad_D1.0mm
U1: ESP32-S3-WROOM-1
U2, U5: SOT-23-6
U3, U4, U32, U37: SOT-23-5
U20, U21, U22: HTSSOP-16-1EP_4.4x5mm_P0.65mm_EP3x3mm
U24: TSSOP-24_4.4x7.8mm_P0.65mm
U25: SOT-353_SC-70-5
U34: SOIC-8_3.9x4.9mm_P1.27mm
U35: TSSOP-8_3x3mm_P0.65mm

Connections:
+3V3_ANALOG: C10.1, C11.1, C17.1, C45.1, FB1.2, R21.1, R43.1, U32.5, U37.5
+3V3_EXT: D7.1, J20.1, R52.2
+3V3_LOGIC: C5.1, C6.1, C13.1, C14.1, C15.1, C16.1, C22.1, FB1.1, J21.2, J22.2, L1.2, R8.1, R9.1, R16.1, R17.1, R23.1, R41.1, R42.1, R48.1, R52.1, R104.1, U1.2, U24.24, U25.5, U35.2, U35.7, U35.8
+3V3_MOTOR: C30.1, C31.1, C32.1, C33.1, C34.1, C35.1, RSH1.2, U20.12, U21.12, U22.12, U32.4
+3V3_MOTOR_REG: C7.1, C8.1, C9.1, RSH1.1, U4.5, U32.3
ADC_CURRENT: C18.1, R20.2, TP1.1, U1.38
ADC_TACHO: R51.2, U1.39
AISEN1: RSA1.1, U20.3
AISEN3: RSA2.1, U21.3
AISEN5: RSA3.1, U22.3
ARM_CLK: C23.2, Q1.3, R25.1, U35.1
ARM_EDGE_IN: C23.1, R24.2
BISEN2: RSB1.1, U20.6
BISEN4: RSB2.1, U21.6
BISEN6: RSB3.1, U22.6
BOOT_N: R9.2, SW2.1, U1.27
CC1: J1.A5, R1.1
CC2: J1.B5, R2.1
COMM_TACHO_N: R48.2, R50.1, TP5.1, U1.31, U34.7
CURRENT_RAW: C44.1, R20.1, TP7.1, U32.1, U34.2
DECODER_INHIBIT: TP4.1, U24.1, U24.23, U25.4
DRIVE_PERMIT: R15.1, U20.1, U21.1, U22.1, U25.2, U35.5
ESP_EN: C12.1, R8.2, SW1.1, U1.3
FAULT_N_RAW: C20.1, R23.2, TP3.1, U2.4, U20.8, U21.8, U22.8, U34.1, U35.6
FLIM_REF: C19.1, R21.2, R22.1, U34.3
FWD1: U20.16, U24.4
FWD2: U20.9, U24.7
FWD3: U21.16, U24.13
FWD4: U21.9, U24.16
FWD5: U22.16, U24.17
FWD6: U22.9, U24.20
GND: C1.2, C2.2, C3.2, C4.2, C5.2, C6.2, C7.2, C8.2, C9.2, C10.2, C11.2, C12.2, C13.2, C14.2, C15.2, C16.2, C17.2, C18.2, C19.2, C20.2, C21.2, C22.2, C30.2, C31.2, C32.2, C33.2, C34.2, C35.2, C43.2, C45.2, D5.2, D7.2, D40.2, D41.2, D42.2, D43.2, D44.2, D45.2, D46.2, D47.2, D48.2, D49.2, D50.2, D51.2, J1.A1, J1.A12, J1.B1, J1.B12, J1.SH, J20.3, J21.1, J22.1, Q1.2, R1.2, R2.2, R5.2, R10.2, R11.2, R12.2, R13.2, R14.2, R15.2, R22.2, R25.2, R44.2, R105.2, RSA1.2, RSA2.2, RSA3.2, RSB1.2, RSB2.2, RSB3.2, SW1.2, SW2.2, U1.1, U1.40, U1.41, U2.2, U3.2, U4.2, U5.2, U20.13, U20.17, U21.13, U21.17, U22.13, U22.17, U24.12, U25.3, U32.2, U34.4, U35.4, U37.2
I2C_SCL: J21.4, R17.2, U1.24
I2C_SDA: J21.3, R16.2, U1.23
LATCH_ARM: R24.1, U1.10
LATCH_STATE: U1.9, U35.3
LOGIC_FB: R104.2, R105.1, U3.5
LOGIC_SW: L1.1, U3.3
MOT1_A: D40.1, J11.2, U20.2
MOT1_B: D41.1, J11.3, U20.4
MOT2_A: D42.1, J12.2, U20.7
MOT2_B: D43.1, J12.3, U20.5
MOT3_A: D44.1, J13.2, U21.2
MOT3_B: D45.1, J13.3, U21.4
MOT4_A: D46.1, J14.2, U21.7
MOT4_B: D47.1, J14.3, U21.5
MOT5_A: D48.1, J15.2, U22.2
MOT5_B: D49.1, J15.3, U22.4
MOT6_A: D50.1, J16.2, U22.7
MOT6_B: D51.1, J16.3, U22.5
MOTOR_ADDR0: R10.1, U1.20, U24.2
MOTOR_ADDR1: R11.1, U1.19, U24.3
MOTOR_ADDR2: R12.1, U1.22, U24.21
MOTOR_ADDR3: R13.1, U1.21, U24.22
MOTOR_ENABLE: Q1.1, R14.1, U1.8, U25.1
ONEWIRE_BUS: D5.1, J20.2, R40.2, R41.2
ONEWIRE_MCU: R40.1, U1.11
REV1: U20.15, U24.5
REV2: U20.10, U24.6
REV3: U21.15, U24.14
REV4: U21.10, U24.15
REV5: U22.15, U24.18
REV6: U22.10, U24.19
STATUS_LED_A: D6.2, R42.2
STATUS_LED_N: D6.1, U1.25
TACHO_AC: C44.2, R45.1, U37.3
TACHO_AMP: C47.1, R46.1, R49.1, R51.1, TP6.1, U37.1
TACHO_CMP: R49.2, R50.2, U34.5
TACHO_FB: C47.2, R46.2, R47.1, U37.4
TACHO_REF: C43.1, R43.2, R44.1, R45.2, R47.2, U34.6
UART_RX_DBG: J22.4, U1.36
UART_TX_DBG: J22.3, U1.37
USB_DM: J1.A7, J1.B7, U1.13, U5.1, U5.6
USB_DP: J1.A6, J1.B6, U1.14, U5.3, U5.4
USB_ILIM: R5.1, U2.5
VBUS_PROTECTED: C2.1, C3.1, C4.1, C21.1, U2.6, U3.1, U3.4, U4.1, U4.3, U34.8
VBUS_RAW: C1.1, J1.A4, J1.A9, J1.B4, J1.B9, U2.1, U2.3, U5.5

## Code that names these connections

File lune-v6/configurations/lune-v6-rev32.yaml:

# =============================================================================
# Lune V6 Rev 3.2 prototype profile
# =============================================================================
# Build:  make config CONFIG=configurations/lune-v6-rev32.yaml BUILD_NAME=lune-v6-rev32
#         make build  CONFIG=configurations/lune-v6-rev32.yaml BUILD_NAME=lune-v6-rev32
#
# Every pin below is the `gpio` map in
# hardware/lune-v6-rev3.2/design-contract.json, which `check_design.py` asserts
# against the schematic.  If they disagree, the contract is right.
#
# This profile must NOT be flashed onto Rev 3.1 hardware and
# `lune-v6-rev31.yaml` must NOT be flashed onto Rev 3.2: ADC_CURRENT moved from
# GPIO4 to GPIO2, GPIO4 is now STATUS_LED_N, GPIO5 lost the BEMF mux, GPIO17
# became LATCH_ARM, and LATCH_STATE on GPIO16 is active *high*.
#
# Automatic motion is disabled on purpose.  The current calibration, the tacho
# band-pass and its pulse-rejection limits are bring-up values derived from
# measured actuator data, not production constants.  Enable motion only on an
# instrumented board, after validating the current offset and gain.
# =============================================================================

substitutions:
  device_name: lune-v6-rev32
  friendly_name: "Lune V6 Rev 3.2 Prototype"
  motor_hardware_backend: rev32_gpio

  # I2C — 4k7 pull-ups fitted (R16/R17)
  pin_i2c_sda: GPIO21
  pin_i2c_scl: GPIO47
  # Protected external bus; a declared ADC1 exception
  pin_onewire: GPIO8

  # MOTOR_ENABLE.  Named nsleep for the shared base; it is a per-move decoder
  # gate, not a global nSLEEP.
  pin_nsleep: "18"
  # LATCH_STATE (/Q of the 74LVC1G74).  High means faulted OR not armed.
  pin_nfault: "16"
  pin_latch_arm: "17"

  # ADC_CURRENT, 10 V/A through the INA180A1, read at 6 dB attenuation
  pin_adc_current: "2"
  # TACHO_AMP — the qualification instrument for the digital count only
  pin_adc_tacho: "1"
  # COMM_TACHO_N, open-collector, counted by PCNT
  pin_comm_tacho: "38"

  # Four plain address bits.  No bit encodes direction; the channel/direction
  # pair maps through the decoder's 12-entry table in rev32_logic.h.
  pin_motor_addr0: "12"
  pin_motor_addr1: "11"
  pin_motor_addr2: "14"
  pin_motor_addr3: "13"

  # D3, a plain KT-0805G green LED through R23 (1k), active low
  pin_status_led: GPIO4

  motor_auto_start_calibration: "false"

packages:
  base: !include ../lune.yaml
  ble:  !include ../packages/hardware/ble.yaml
  led:  !include ../packages/hardware/led-mono.yaml

# The production-intent module is ESP32-S3-WROOM-1-N8R8: 8 MB flash, octal
# PSRAM.  A PlatformIO board description that says "No PSRAM" is generic board
# metadata and is not the effective sdkconfig.
esphome:
  platformio_options:
    board_build.psram_type: opi

esp32:
  flash_size: 8MB
  framework:
    sdkconfig_options:
      CONFIG_ESPTOOLPY_FLASHSIZE_8MB: "y"

psram:
  mode: octal
  speed: 80MHz
  ignore_not_found: false

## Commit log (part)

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2026-06-26 Prepare Lune V6 brand structure
2026-06-26 Extract coordinator-owned forecast preload
2026-06-27 Add mock dashboard HTML and design system documentation for Lune V6
    - Created a new mock dashboard HTML file to facilitate local testing.
    - Added a README for shared dashboard notes, outlining the purpose and future plans for shared UI patterns.
    - Introduced a comprehensive design system document detailing color palettes, typography, spacing, border radius, shadows, and responsive breakpoints for the Lune V6 UI.
2026-06-29 Add initial configuration files and diagnostics for Lune Touch device
    - Created api.yaml for API configuration with encryption key.
    - Added ota.yaml for OTA updates with password and safe mode settings.
    - Introduced wifi.yaml for WiFi configuration with fallback AP settings.
    - Implemented diagnostics.yaml for system diagnostics including WiFi signal and uptime sensors.
    - Defined partition scheme in lune_touch_16mb_ota.csv for memory management.
    - Added unit tests for coordinator model functionality in test_coordinator_model.cpp.
2026-06-29 Add Lune Touch dashboard shell
2026-06-29 Extend V6 API for coordinator resources
2026-06-29 Persist Lune Touch coordinator registry
2026-06-29 Add Touch live zone snapshots
2026-06-29 Persist Touch command ledger
2026-06-29 Add Touch dashboard mapping controls
2026-06-29 Add Touch live binding updates
2026-06-29 Poll V6 zones from Lune Touch
2026-06-29 Forward Touch setpoint commands to V6
2026-06-29 Show Touch command expiry in dashboard
2026-06-29 Expose Touch polling diagnostics
2026-06-29 Show Touch polling diagnostics
2026-06-29 Fetch Open-Meteo from Touch coordinator
2026-06-29 Add Touch forecast dashboard controls
2026-06-29 Add Lune Touch deploy targets
2026-06-29 Poll V6 overview from Touch
2026-06-29 Disable Touch mock polling on hardware
2026-06-29 Stabilize Touch dashboard responses
2026-06-29 Reduce Touch dashboard auto refresh
2026-06-29 Add Lune Touch monitor targets
